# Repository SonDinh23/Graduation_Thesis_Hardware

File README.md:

# Graduation_Thesis_Hardware
Graduation_Thesis_Hardware

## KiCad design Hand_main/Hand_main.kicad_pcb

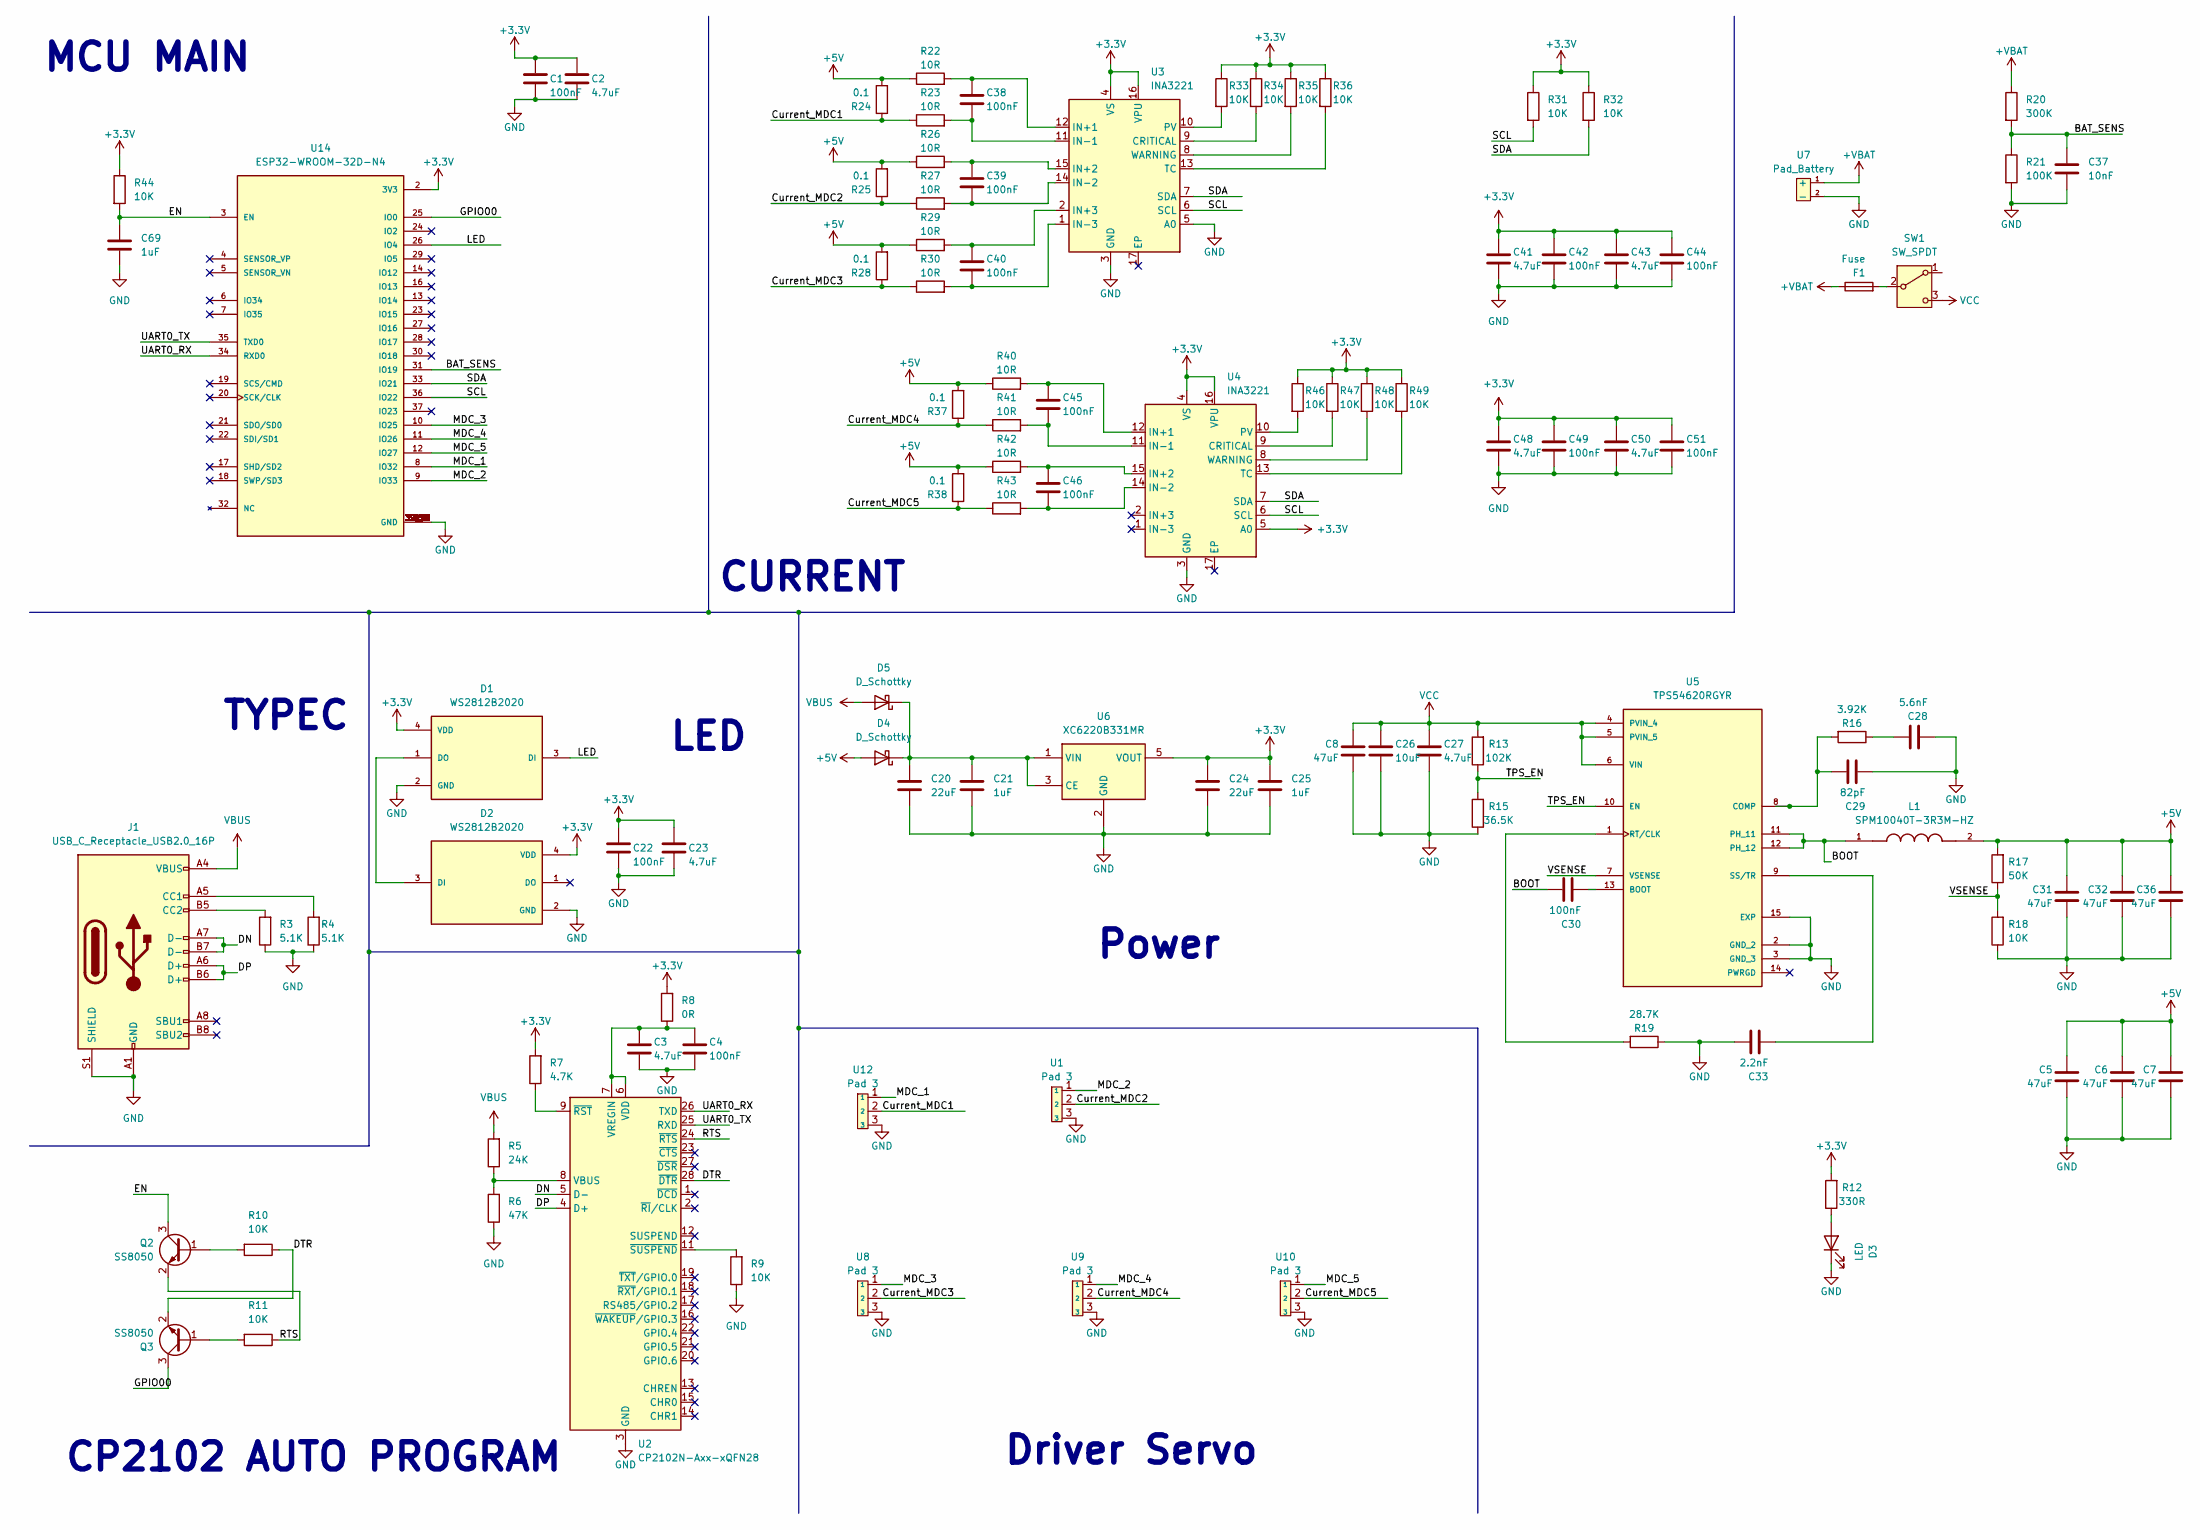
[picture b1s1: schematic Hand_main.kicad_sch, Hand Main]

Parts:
C1, C4, C22, C30, C38, C39, C40, C42, C44, C45, C46, C49, C51: 100nF; C_0402_1005Metric
C2, C3, C23, C41, C43, C48, C50: 4.7uF; C_0402_1005Metric
C5, C6, C7, C8, C31, C32, C36: 47uF; C_0805_2012Metric
C20, C24: 22uF; C_0603_1608Metric
C21, C25: 1uF; C_0603_1608Metric
C26: 10uF; C_0603_1608Metric
C27: 4.7uF; C_0603_1608Metric
C28: 5.6nF; C_0402_1005Metric
C29: 82pF; C_0402_1005Metric
C33: 2.2nF; C_0402_1005Metric
C37: 10nF; C_0402_1005Metric
C69: 1uF; C_0402_1005Metric
D1, D2: WS2812B2020; LED_WS2812B2020; PARTREV V1.0
D3: LED; LED_0805_2012Metric
D4, D5: D_Schottky; D_SOD-123
F1: Fuse; Fuse_1812_4532Metric
J1: USB_C_Receptacle_USB2.0_16P; USB_C_Receptacle_GCT_USB4105-xx-A_16P_TopMnt_Horizontal
L1: SPM10040T-3R3M-HZ; IND_SPM10040T-3R3M-HZ; PARTREV 20210512
Q2, Q3: SS8050; SOT-23
R3, R4: 5.1K; C_0402_1005Metric
R5: 24K; C_0402_1005Metric
R6: 47K; C_0402_1005Metric
R7: 4.7K; C_0402_1005Metric
R8: 0R; C_0402_1005Metric
R9, R10, R11, R18, R31, R32, R33, R34, R35, R36, R44, R46, R47, R48, R49: 10K; C_0402_1005Metric
R12: 330R; C_0402_1005Metric
R13: 102K; C_0402_1005Metric
R15: 36.5K; C_0402_1005Metric
R16: 3.92K; C_0402_1005Metric
R17: 50K; C_0402_1005Metric
R19: 28.7K; C_0402_1005Metric
R20: 300K; C_0402_1005Metric
R21: 100K; C_0402_1005Metric
R22, R23, R26, R27, R29, R30, R40, R41, R42, R43: 10R; C_0402_1005Metric
R24, R25, R28, R37, R38: 0.1; R_2512_6332Metric
SW1: SW_SPDT; SS-12D06G5
U1, U8, U9, U10, U12: Pad 3
U2: CP2102N-Axx-xQFN28; QFN-28-1EP_5x5mm_P0.5mm_EP3.35x3.35mm
U3, U4: INA3221; Texas_RGV0016A_VQFN-16-1EP_4x4mm_P0.65mm_EP2.1x2.1mm
U5: TPS54620RGYR; QFN50P350X350X100-15N; PARTREV 06/2011
U6: XC6220B331MR; SOT-23-5
U7: Pad_Battery; JST_XH_B2B-XH-AM_1x02_P2.50mm_Vertical
U14: ESP32-WROOM-32D-N4; ESP32-WROOM-32D; PARTREV 1.9

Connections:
+3.3V: C1.1, C2.1, C22.1, C23.1, C24.1, C25.1, C41.1, C42.1, C43.1, C44.1, C48.1, C49.1, C50.1, C51.1, D1.4 (VDD), D2.4 (VDD), R7.2, R8.2, R12.2, R31.1, R32.1, R33.1, R34.1, R35.1, R36.1, R44.1, R46.1, R47.1, R48.1, R49.1, U3.4 (VS), U3.16 (VPU), U4.4 (VS), U4.5 (A0), U4.16 (VPU), U6.5 (VOUT), U14.2 (3V3)
+5V: C5.2, C6.2, C7.2, C31.2, C32.2, C36.2, D4.2 (A), L1.2, R17.2, R22.1, R24.2, R25.2, R26.1, R28.2, R29.1, R37.2, R38.2, R40.1, R42.1
+VBAT: F1.1, R20.1, U7.1 (+)
/BAT_SENS: C37.1, R20.2, R21.1, U14.31 (IO19)
/BOOT: C30.1, L1.1, U5.11 (PH_11), U5.12 (PH_12)
/Current_MDC1: R23.1, R24.1, U12.2
/Current_MDC2: R25.1, R27.1, U1.2
/Current_MDC3: R28.1, R30.1, U8.2
/Current_MDC4: R37.1, R41.1, U9.2
/Current_MDC5: R38.1, R43.1, U10.2
/DN: J1.A7 (D-), J1.B7 (D-), U2.5 (D-)
/DP: J1.A6 (D+), J1.B6 (D+), U2.4 (D+)
/DTR: Q3.2 (E), R10.1, U2.28 (~DTR)
/EN: C69.1, Q2.3 (C), R44.2, U14.3 (EN)
/GPIO00: Q3.3 (C), U14.25 (IO0)
/LED: D1.3 (DI), U14.26 (IO4)
/MDC_1: U12.1, U14.8 (IO32)
/MDC_2: U1.1, U14.9 (IO33)
/MDC_3: U8.1, U14.10 (IO25)
/MDC_4: U9.1, U14.11 (IO26)
/MDC_5: U10.1, U14.12 (IO27)
/RTS: Q2.2 (E), R11.1, U2.24 (~RTS)
/SCL: R31.2, U3.6 (SCL), U4.6 (SCL), U14.36 (IO22)
/SDA: R32.2, U3.7 (SDA), U4.7 (SDA), U14.33 (IO21)
/TPS_EN: R13.1, R15.2, U5.10 (EN)
/UART0_RX: U2.26 (TXD), U14.34 (RXD0)
/UART0_TX: U2.25 (RXD), U14.35 (TXD0)
/VSENSE: R17.1, R18.2, U5.7 (VSENSE)
GND: C1.2, C2.2, C3.2, C4.2, C5.1, C6.1, C7.1, C8.1, C20.2, C21.2, C22.2, C23.2, C24.2, C25.2, C26.2, C27.2, C28.2, C29.2, C31.1, C32.1, C33.1, C36.1, C37.2, C41.2, C42.2, C43.2, C44.2, C48.2, C49.2, C50.2, C51.2, C69.2, D1.2 (GND), D2.2 (GND), D3.1 (K), J1.A1 (GND), J1.A12 (GND), J1.B1 (GND), J1.B12 (GND), J1.S1 (SHIELD), R3.1, R4.1, R6.1, R9.1, R15.1, R18.1, R19.1, R21.2, U1.3, U2.3 (GND), U2.29 (GND), U3.3 (GND), U3.5 (A0), U4.3 (GND), U5.2 (GND_2), U5.3 (GND_3), U5.15 (EXP), U6.2 (GND), U7.2 (-), U8.3, U9.3, U10.3, U12.3, U14.1 (GND), U14.15 (GND), U14.38 (GND), U14.39_1 (GND), U14.39_2 (GND), U14.39_3 (GND), U14.39_4 (GND), U14.39_5 (GND), U14.39_6 (GND), U14.39_7 (GND), U14.39_8 (GND), U14.39_9 (GND), U14.39_10 (GND), U14.39_11 (GND), U14.39_12 (GND), U14.39_13 (GND), U14.39_14 (GND), U14.39_15 (GND), U14.39_16 (GND), U14.39_17 (GND), U14.39_18 (GND), U14.39_19 (GND), U14.39_20 (GND), U14.39_21 (GND)
unnamed: C28.1, R16.1
unnamed: D1.1 (DO), D2.3 (DI)
unnamed: D3.2 (A), R12.1
unnamed: C20.1, C21.1, D4.1 (K), D5.1 (K), U6.1 (VIN), U6.3 (CE)
unnamed: J1.A5 (CC1), R4.2
unnamed: J1.B5 (CC2), R3.2
unnamed: Q2.1 (B), R10.2
unnamed: Q3.1 (B), R11.2
unnamed: F1.2, SW1.2 (B)
unnamed: R5.1, R6.2, U2.8 (VBUS)
unnamed: C3.1, C4.1, R8.1, U2.6 (VDD), U2.7 (VREGIN)
unnamed: R7.1, U2.9 (~RST)
unnamed: R9.2, U2.11 (~SUSPEND)
unnamed: R34.2, U3.9 (CRITICAL)
unnamed: C38.1, R22.2, U3.12 (IN+1)
unnamed: C39.1, R26.2, U3.15 (IN+2)
unnamed: C40.1, R29.2, U3.2 (IN+3)
unnamed: C38.2, R23.2, U3.11 (IN-1)
unnamed: C39.2, R27.2, U3.14 (IN-2)
unnamed: C40.2, R30.2, U3.1 (IN-3)
unnamed: R33.2, U3.10 (PV)
unnamed: R36.2, U3.13 (TC)
unnamed: R35.2, U3.8 (WARNING)
unnamed: R47.2, U4.9 (CRITICAL)
unnamed: C45.1, R40.2, U4.12 (IN+1)
unnamed: C46.1, R42.2, U4.15 (IN+2)
unnamed: C45.2, R41.2, U4.11 (IN-1)
unnamed: C46.2, R43.2, U4.14 (IN-2)
unnamed: R46.2, U4.10 (PV)
unnamed: R49.2, U4.13 (TC)
unnamed: R48.2, U4.8 (WARNING)
unnamed: C30.2, U5.13 (BOOT)
unnamed: C29.1, R16.2, U5.8 (COMP)
unnamed: R19.2, U5.1 (RT/CLK)
unnamed: C33.2, U5.9 (SS/TR)
VBUS: D5.2 (A), J1.A4 (VBUS), J1.A9 (VBUS), J1.B4 (VBUS), J1.B9 (VBUS), R5.2
VCC: C8.2, C26.1, C27.1, R13.2, SW1.3 (C), U5.4 (PVIN_4), U5.5 (PVIN_5), U5.6 (VIN)

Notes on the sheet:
CP2102 AUTO PROGRAM
Power
CURRENT
TYPEC
Driver Servo
MCU MAIN
LED

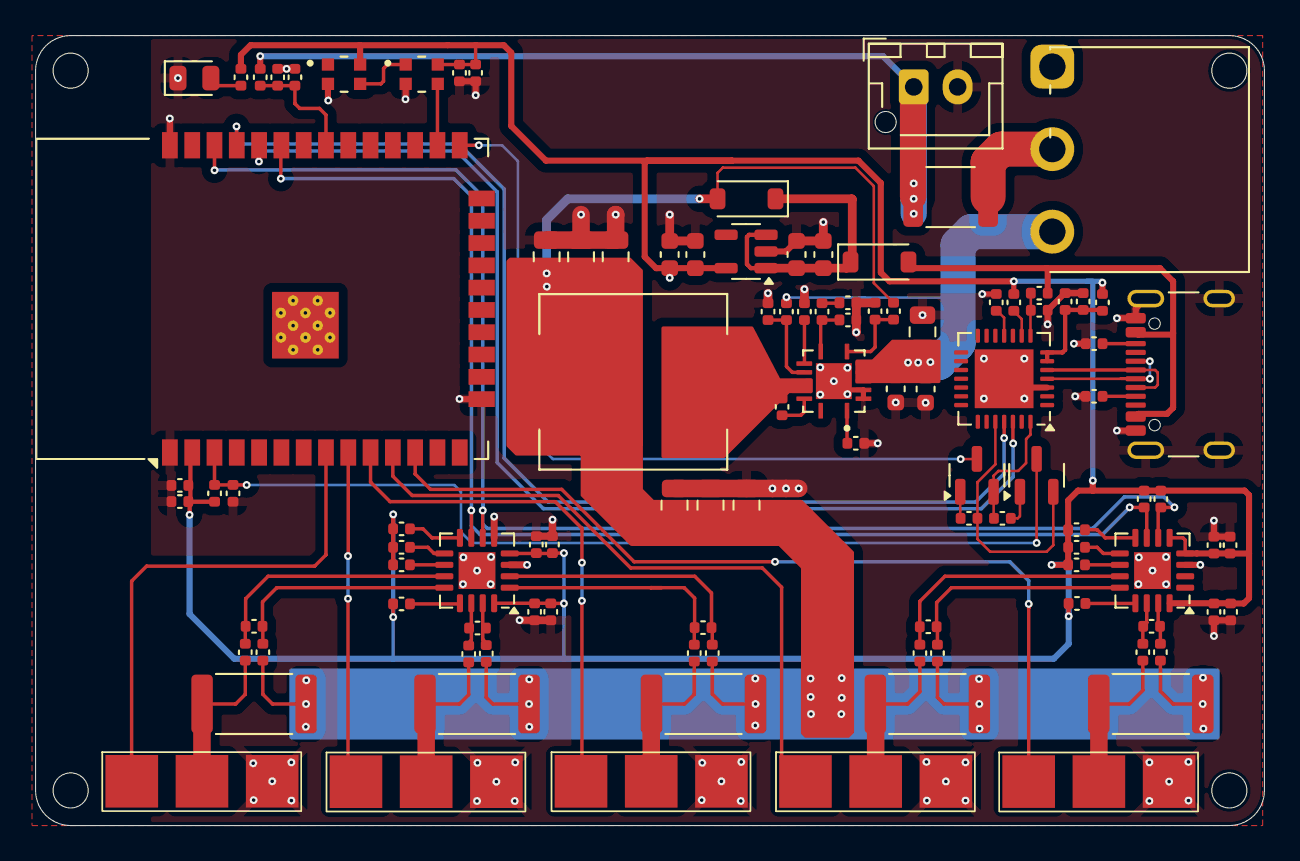
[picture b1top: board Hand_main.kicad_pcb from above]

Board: 4 copper layers, 70.0 x 45.0 mm, 105 parts (0 on the bottom side), 66 nets.

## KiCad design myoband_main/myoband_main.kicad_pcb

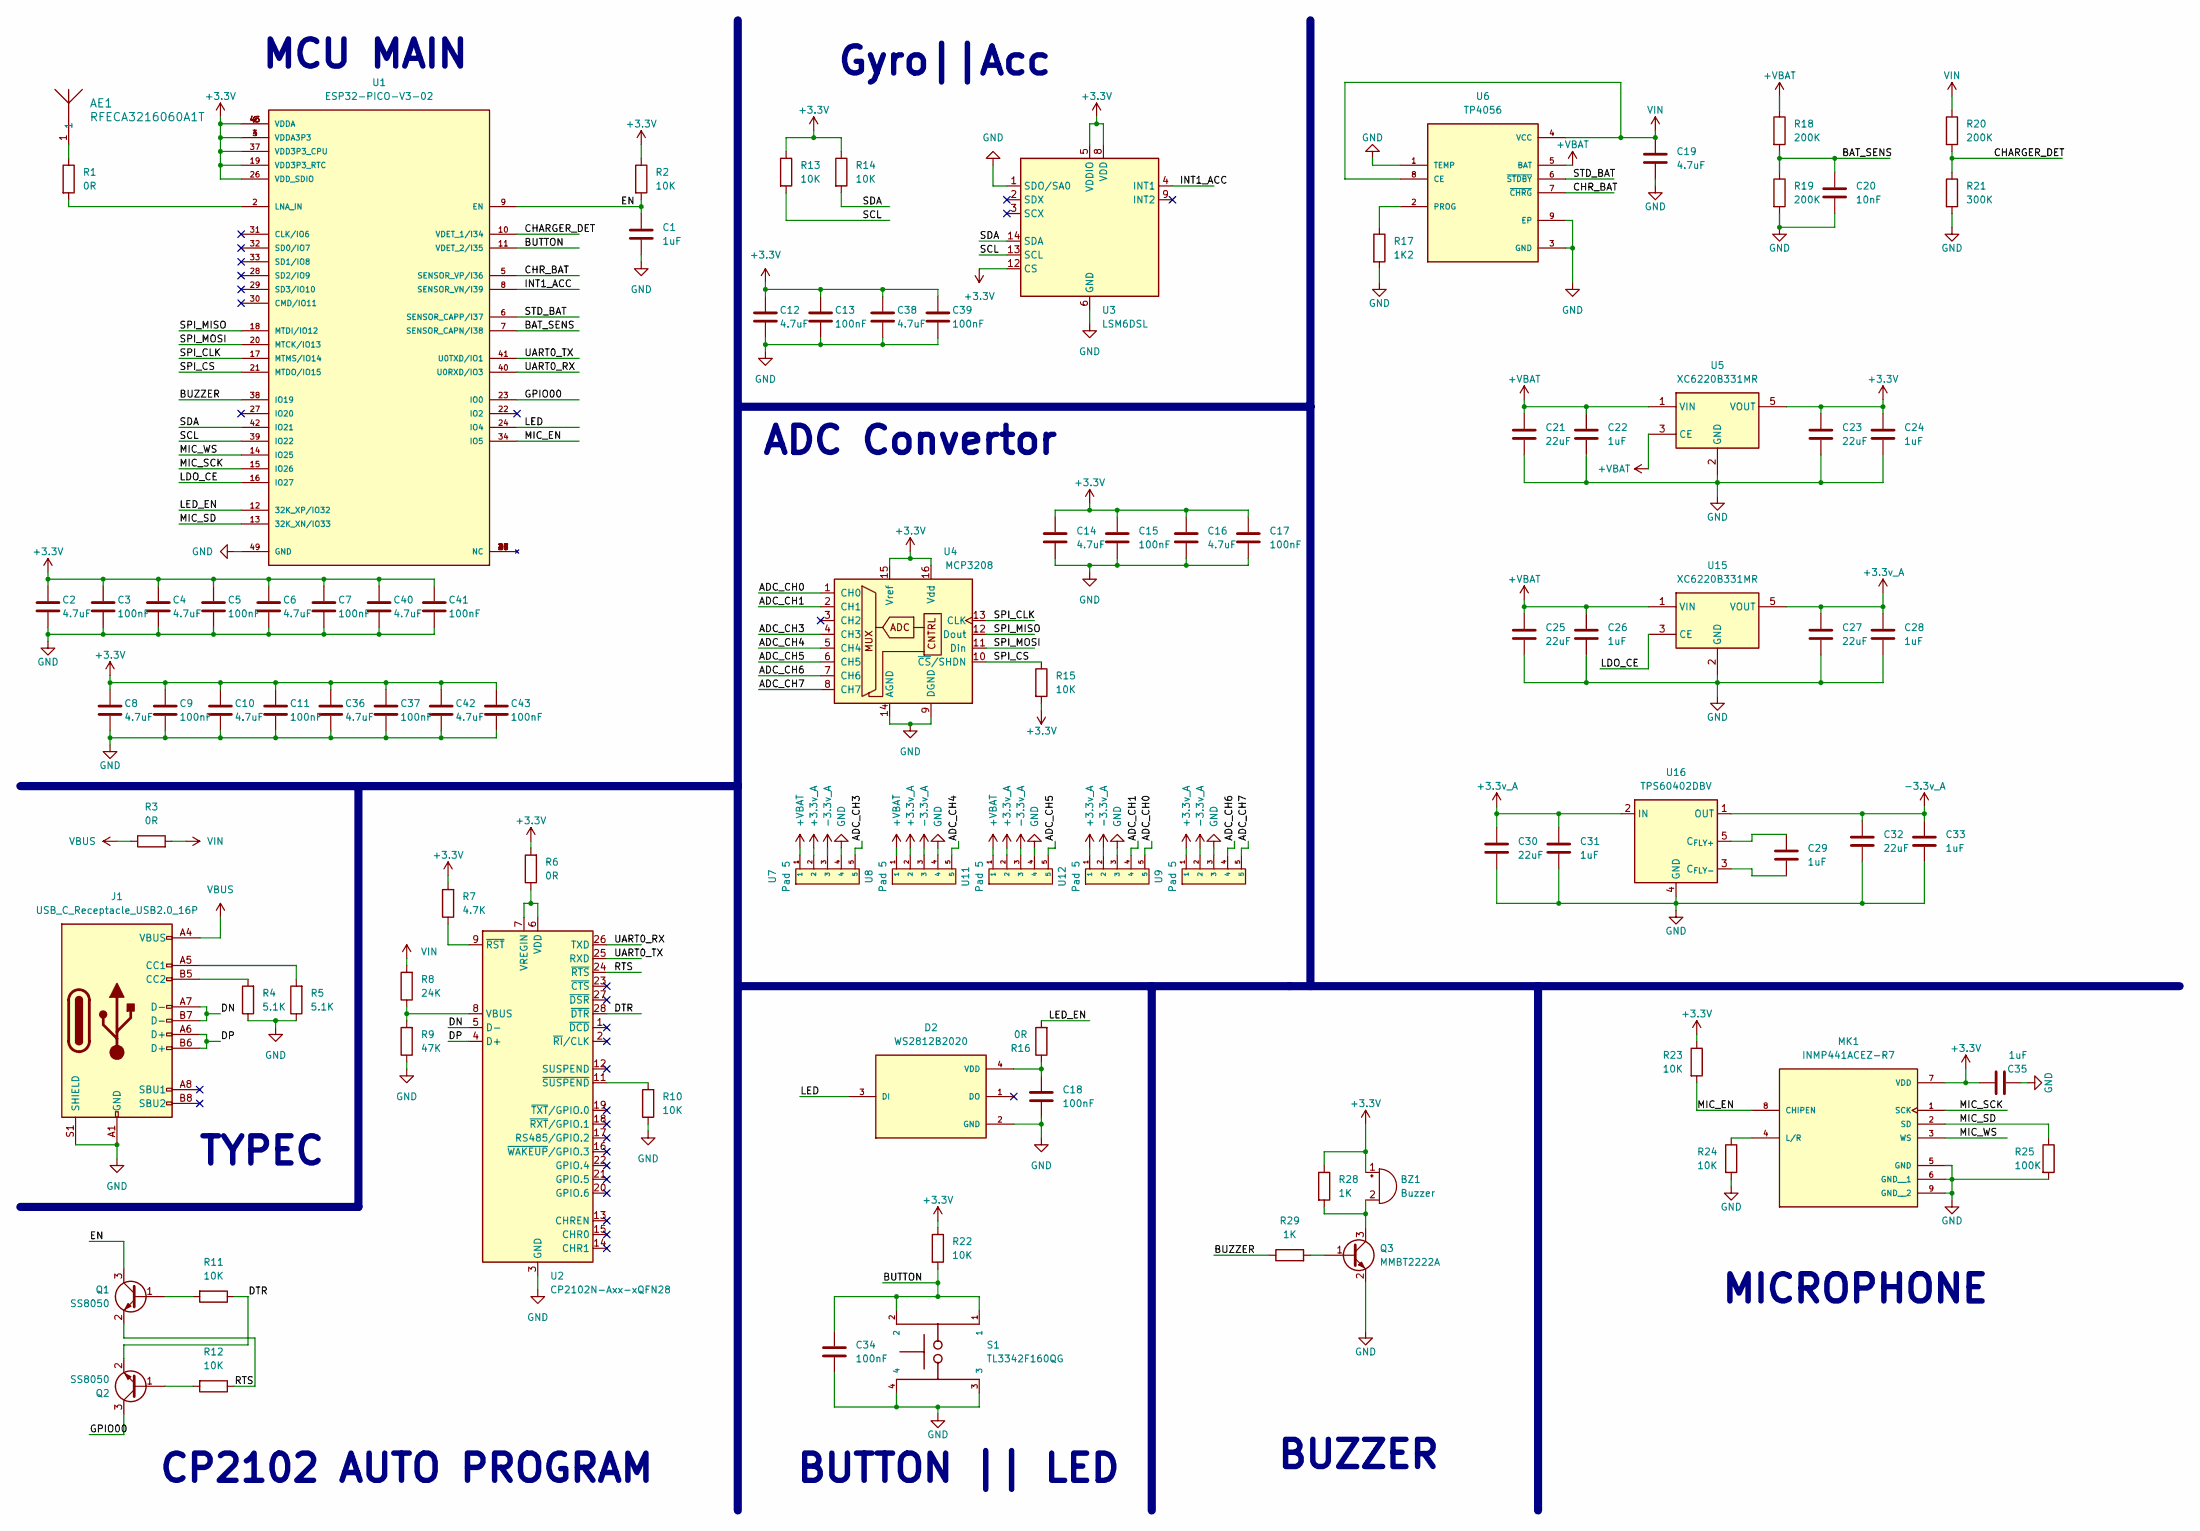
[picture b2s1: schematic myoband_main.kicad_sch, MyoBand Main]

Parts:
AE1: RFECA3216060A1T; ANT_16060A1T_WAL
BZ1: Buzzer; Buzzer_Murata_PKMCS0909E
C1, C22, C24, C26, C28, C29, C31, C33, C35: 1uF; C_0402_1005Metric
C2, C4, C6, C8, C10, C12, C14, C16, C19, C36, C38, C40, C42: 4.7uF; C_0402_1005Metric
C3, C5, C7, C9, C11, C13, C15, C17, C18, C34, C37, C39, C41, C43: 100nF; C_0402_1005Metric
C20: 10nF; C_0402_1005Metric
C21, C23, C25, C27, C30, C32: 22uF; C_0603_1608Metric
D2: WS2812B2020; LED_WS2812B2020; PARTREV V1.0
J1: USB_C_Receptacle_USB2.0_16P; USB_C_Receptacle_GCT_USB4105-xx-A_16P_TopMnt_Horizontal
MK1: INMP441ACEZ-R7; MIC_INMP441ACEZ-R7; PARTREV 1.1
Q1, Q2: SS8050; SOT-23
Q3: MMBT2222A; SOT-23
R1, R3, R6, R16: 0R; C_0402_1005Metric
R2, R10, R11, R12, R13, R14, R15, R22, R23, R24: 10K; C_0402_1005Metric
R4, R5: 5.1K; C_0402_1005Metric
R7: 4.7K; C_0402_1005Metric
R8: 24K; C_0402_1005Metric
R9: 47K; C_0402_1005Metric
R17: 1K2; C_0402_1005Metric
R18, R19, R20: 200K; C_0402_1005Metric
R21: 300K; C_0402_1005Metric
R25: 100K; C_0402_1005Metric
R28, R29: 1K; C_0402_1005Metric
S1: TL3342F160QG; SW_TL3342F160QG
U1: ESP32-PICO-V3-02; XCVR_ESP32-PICO-V3-02; PARTREV 1.0
U2: CP2102N-Axx-xQFN28; QFN-28-1EP_5x5mm_P0.5mm_EP3.35x3.35mm
U3: LSM6DSL; LGA-14_3x2.5mm_P0.5mm_LayoutBorder3x4y
U4: MCP3208; SOIC-16_3.9x9.9mm_P1.27mm
U5, U15: XC6220B331MR; SOT-23-5
U6: TP4056; SOP127P600X175-9N
U7, U8, U9, U11, U12: Pad 5
U16: TPS60402DBV; SOT-23-5

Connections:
+3.3V: BZ1.1 (+), C2.1, C3.1, C4.1, C5.1, C6.1, C7.1, C8.1, C9.1, C10.1, C11.1, C12.1, C13.1, C14.1, C15.1, C16.1, C17.1, C23.1, C24.1, C35.1, C36.1, C37.1, C38.1, C39.1, C40.1, C41.1, C42.1, C43.1, MK1.7 (VDD), R2.1, R6.2, R7.2, R13.1, R14.1, R15.2, R22.1, R23.1, R28.1, U1.1 (VDDA), U1.3 (VDDA3P3), U1.4 (VDDA3P3), U1.19 (VDD3P3_RTC), U1.26 (VDD_SDIO), U1.37 (VDD3P3_CPU), U1.43 (VDDA), U1.46 (VDDA), U3.5 (VDDIO), U3.8 (VDD), U3.12 (CS), U4.15 (Vref), U4.16 (Vdd), U5.5 (VOUT)
+3.3v_A: C27.1, C28.1, C30.1, C31.1, U7.2, U8.2, U9.1, U11.2, U12.1, U15.5 (VOUT), U16.2 (IN)
+VBAT: C21.1, C22.1, C25.1, C26.1, R18.1, U5.1 (VIN), U5.3 (CE), U6.5 (BAT), U7.1, U8.1, U11.1, U15.1 (VIN)
-3.3v_A: C32.1, C33.1, U7.3, U8.3, U9.2, U11.3, U12.2, U16.1 (OUT)
/ADC_CH0: U4.1 (CH0), U12.5
/ADC_CH1: U4.2 (CH1), U12.4
/ADC_CH3: U4.4 (CH3), U7.5
/ADC_CH4: U4.5 (CH4), U8.5
/ADC_CH5: U4.6 (CH5), U11.5
/ADC_CH6: U4.7 (CH6), U9.4
/ADC_CH7: U4.8 (CH7), U9.5
/BAT_SENS: C20.1, R18.2, R19.1, U1.7 (SENSOR_CAPN/I38)
/BUTTON: C34.1, R22.2, S1.1, S1.2, U1.11 (VDET_2/I35)
/BUZZER: R29.1, U1.38 (IO19)
/CHARGER_DET: R20.2, R21.1, U1.10 (VDET_1/I34)
/CHR_BAT: U1.5 (SENSOR_VP/I36), U6.7 (~CHRG)
/DN: J1.A7 (D-), J1.B7 (D-), U2.5 (D-)
/DP: J1.A6 (D+), J1.B6 (D+), U2.4 (D+)
/DTR: Q2.2 (E), R11.1, U2.28 (~DTR)
/EN: C1.1, Q1.3 (C), R2.2, U1.9 (EN)
/GPIO00: Q2.3 (C), U1.23 (IO0)
/INT1_ACC: U1.8 (SENSOR_VN/I39), U3.4 (INT1)
/LDO_CE: U1.16 (IO27), U15.3 (CE)
/LED: D2.3 (DI), U1.24 (IO4)
/LED_EN: R16.2, U1.12 (32K_XP/IO32)
/MIC_EN: MK1.8 (CHIPEN), R23.2, U1.34 (IO5)
/MIC_SCK: MK1.1 (SCK), U1.15 (IO26)
/MIC_SD: MK1.2 (SD), R25.1, U1.13 (32K_XN/IO33)
/MIC_WS: MK1.3 (WS), U1.14 (IO25)
/RTS: Q1.2 (E), R12.1, U2.24 (~RTS)
/SCL: R13.2, U1.39 (IO22), U3.13 (SCL)
/SDA: R14.2, U1.42 (IO21), U3.14 (SDA)
/SPI_CLK: U1.17 (MTMS/IO14), U4.13 (CLK)
/SPI_CS: R15.1, U1.21 (MTDO/IO15), U4.10 (~CS/SHDN)
/SPI_MISO: U1.18 (MTDI/IO12), U4.12 (Dout)
/SPI_MOSI: U1.20 (MTCK/IO13), U4.11 (Din)
/STD_BAT: U1.6 (SENSOR_CAPP/I37), U6.6 (~STDBY)
/UART0_RX: U1.40 (U0RXD/IO3), U2.26 (TXD)
/UART0_TX: U1.41 (U0TXD/IO1), U2.25 (RXD)
GND: C1.2, C2.2, C3.2, C4.2, C5.2, C6.2, C7.2, C8.2, C9.2, C10.2, C11.2, C12.2, C13.2, C14.2, C15.2, C16.2, C17.2, C18.2, C19.2, C20.2, C21.2, C22.2, C23.2, C24.2, C25.2, C26.2, C27.2, C28.2, C30.2, C31.2, C32.2, C33.2, C34.2, C35.2, C36.2, C37.2, C38.2, C39.2, C40.2, C41.2, C42.2, C43.2, D2.2 (GND), J1.A1 (GND), J1.A12 (GND), J1.B1 (GND), J1.B12 (GND), J1.S1 (SHIELD), MK1.5 (GND), MK1.6 (GND__1), MK1.9 (GND__2), Q3.2 (E), R4.1, R5.1, R9.1, R10.1, R17.2, R19.2, R21.2, R24.2, R25.2, S1.3, S1.4, U1.49 (GND), U2.3 (GND), U2.29 (GND), U3.1 (SDO/SA0), U3.6 (GND), U3.7 (GND), U4.9 (DGND), U4.14 (AGND), U5.2 (GND), U6.1 (TEMP), U6.3 (GND), U6.9 (EP), U7.4, U8.4, U9.3, U11.4, U12.3, U15.2 (GND), U16.4 (GND)
unnamed: AE1.1, R1.1
unnamed: BZ1.2 (-), Q3.3 (C), R28.2
unnamed: C18.1, D2.4 (VDD), R16.1
unnamed: J1.A5 (CC1), R5.2
unnamed: J1.B5 (CC2), R4.2
unnamed: MK1.4 (L/R), R24.1
unnamed: Q1.1 (B), R11.2
unnamed: Q2.1 (B), R12.2
unnamed: Q3.1 (B), R29.2
unnamed: R1.2, U1.2 (LNA_IN)
unnamed: R8.1, R9.2, U2.8 (VBUS)
unnamed: R6.1, U2.6 (VDD), U2.7 (VREGIN)
unnamed: R7.1, U2.9 (~RST)
unnamed: R10.2, U2.11 (~SUSPEND)
unnamed: R17.1, U6.2 (PROG)
unnamed: C29.1, U16.5 (C_{FLY+})
unnamed: C29.2, U16.3 (C_{FLY-})
VBUS: J1.A4 (VBUS), J1.A9 (VBUS), J1.B4 (VBUS), J1.B9 (VBUS), R3.1
VIN: C19.1, R3.2, R8.2, R20.1, U6.4 (VCC), U6.8 (CE)

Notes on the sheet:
MCU MAIN
TYPEC
BUTTON || LED
Gyro||Acc
MICROPHONE
CP2102 AUTO PROGRAM
BUZZER
ADC Convertor

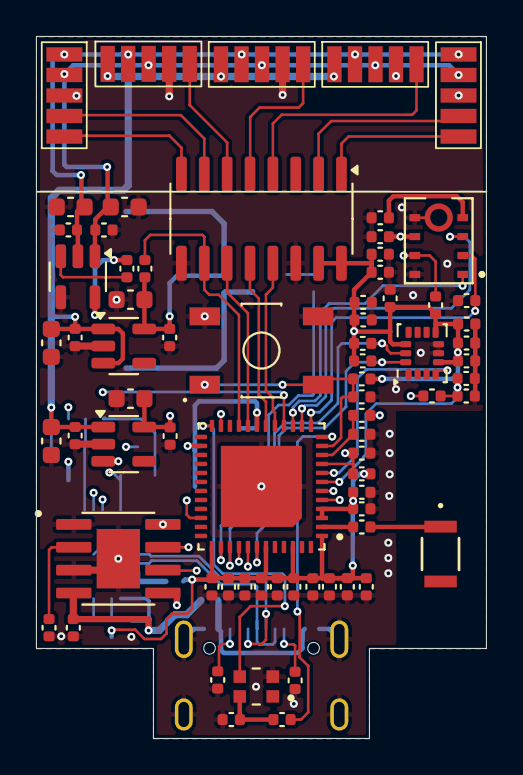
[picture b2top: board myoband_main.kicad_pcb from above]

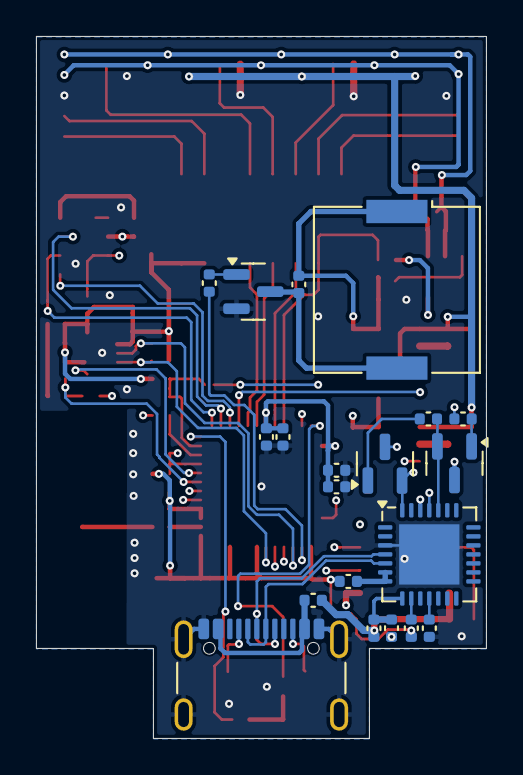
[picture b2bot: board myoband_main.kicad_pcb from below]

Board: 4 copper layers, 25.0 x 39.0 mm, 92 parts (20 on the bottom side), 59 nets.

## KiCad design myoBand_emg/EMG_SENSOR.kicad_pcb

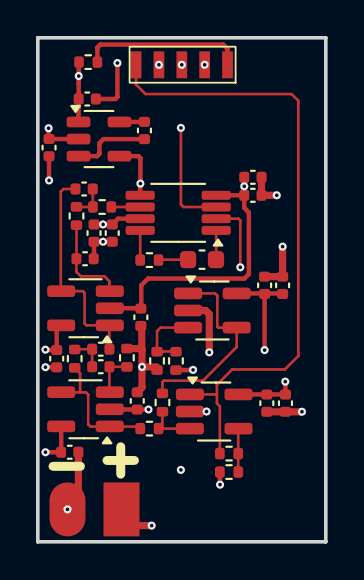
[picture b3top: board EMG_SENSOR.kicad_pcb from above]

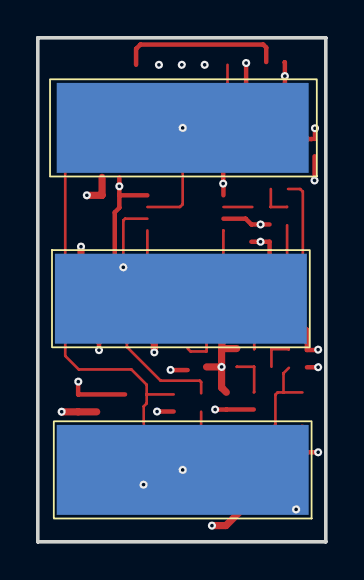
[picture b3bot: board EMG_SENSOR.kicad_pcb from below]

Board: 4 copper layers, 16.0 x 28.0 mm, 43 parts (3 on the bottom side), 24 nets.

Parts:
C1, C7, C9, C20: 4.7uF; C_0402_1005Metric
C2, C4, C6, C8, C10, C13, C14, C16, C17, C18, C19, C21: 100nF; C_0402_1005Metric
C5, C12, C22: 1uF; C_0402_1005Metric
C11: 10uF; C_0603_1608Metric
R1: 220R; R_0402_1005Metric
R2: 3.6K; R_0402_1005Metric
R3: 2.8K; R_0402_1005Metric
R4: 0R/NC; R_0402_1005Metric
R6: 33K; R_0402_1005Metric
R7: 22K; R_0402_1005Metric
R8, R9: 100K; R_0402_1005Metric
R10, R13: 2K; R_0402_1005Metric
R11, R12: 1K; R_0402_1005Metric
U1: INA333xxDGK; VSSOP-8_3x3mm_P0.65mm
U2, U3, U4, U5: MCP601-xOT; SOT-23-5_HandSoldering
U6: Pad 5
U7: Pad_Battery; Pad Battery
U8, U9, U10: Pad_1; Pad 1
U11: TPS60402DBV; SOT-23-5

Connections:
+1.65V: R11.2, U3.1, U3.4 (-)
+3.3v_A: C1.1, C2.1, C4.1, C5.1, C7.1, C8.1, C13.1, C20.1, C21.1, R8.2, U1.7 (V+), U2.5 (V+), U3.5 (V+), U4.5 (V+), U5.5 (V+), U6.3, U11.2 (IN)
+VBAT: U6.2, U7.1 (+)
-3.3v_A: C6.2, C9.1, C10.1, C14.2, C22.1, R4.2, U1.4 (V-), U2.2 (V-), U4.2 (V-), U11.1 (OUT)
-3.3v_IN: R4.1, U6.1
/ADC_OUT: R12.1, U5.1, U6.5
/E_END: U1.3 (+), U8.1 (S)
/E_MID: U1.2 (-), U9.1 (S)
/OUT_Amplifer: R2.1, U1.6
/OUT_HP: R7.1, R10.1, U4.1, U4.4 (-)
/OUT_LP: C17.1, C18.2, U2.1, U2.4 (-)
GND: C1.2, C2.2, C4.2, C5.2, C6.1, C7.2, C8.2, C9.2, C10.2, C13.2, C14.1, C16.1, C20.2, C21.2, C22.2, R6.1, R9.1, R13.2, U1.5 (Ref), U3.2 (V-), U5.2 (V-), U6.4, U7.2 (-), U10.1 (S), U11.4 (GND)
unnamed: C11.1, R1.1
unnamed: C11.2, U1.1 (Rg)
unnamed: C17.2, R2.2, R3.1
unnamed: C18.1, C19.2, R7.2
unnamed: R1.2, U1.8 (Rg)
unnamed: C16.2, R3.2, U2.3 (+)
unnamed: R8.1, R9.2, U3.3 (+)
unnamed: C19.1, R6.2, U4.3 (+)
unnamed: R10.2, R11.1, U5.3 (+)
unnamed: R12.2, R13.1, U5.4 (-)
unnamed: C12.1, U11.5 (C_{FLY+})
unnamed: C12.2, U11.3 (C_{FLY-})

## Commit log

2025-06-20 first upload
